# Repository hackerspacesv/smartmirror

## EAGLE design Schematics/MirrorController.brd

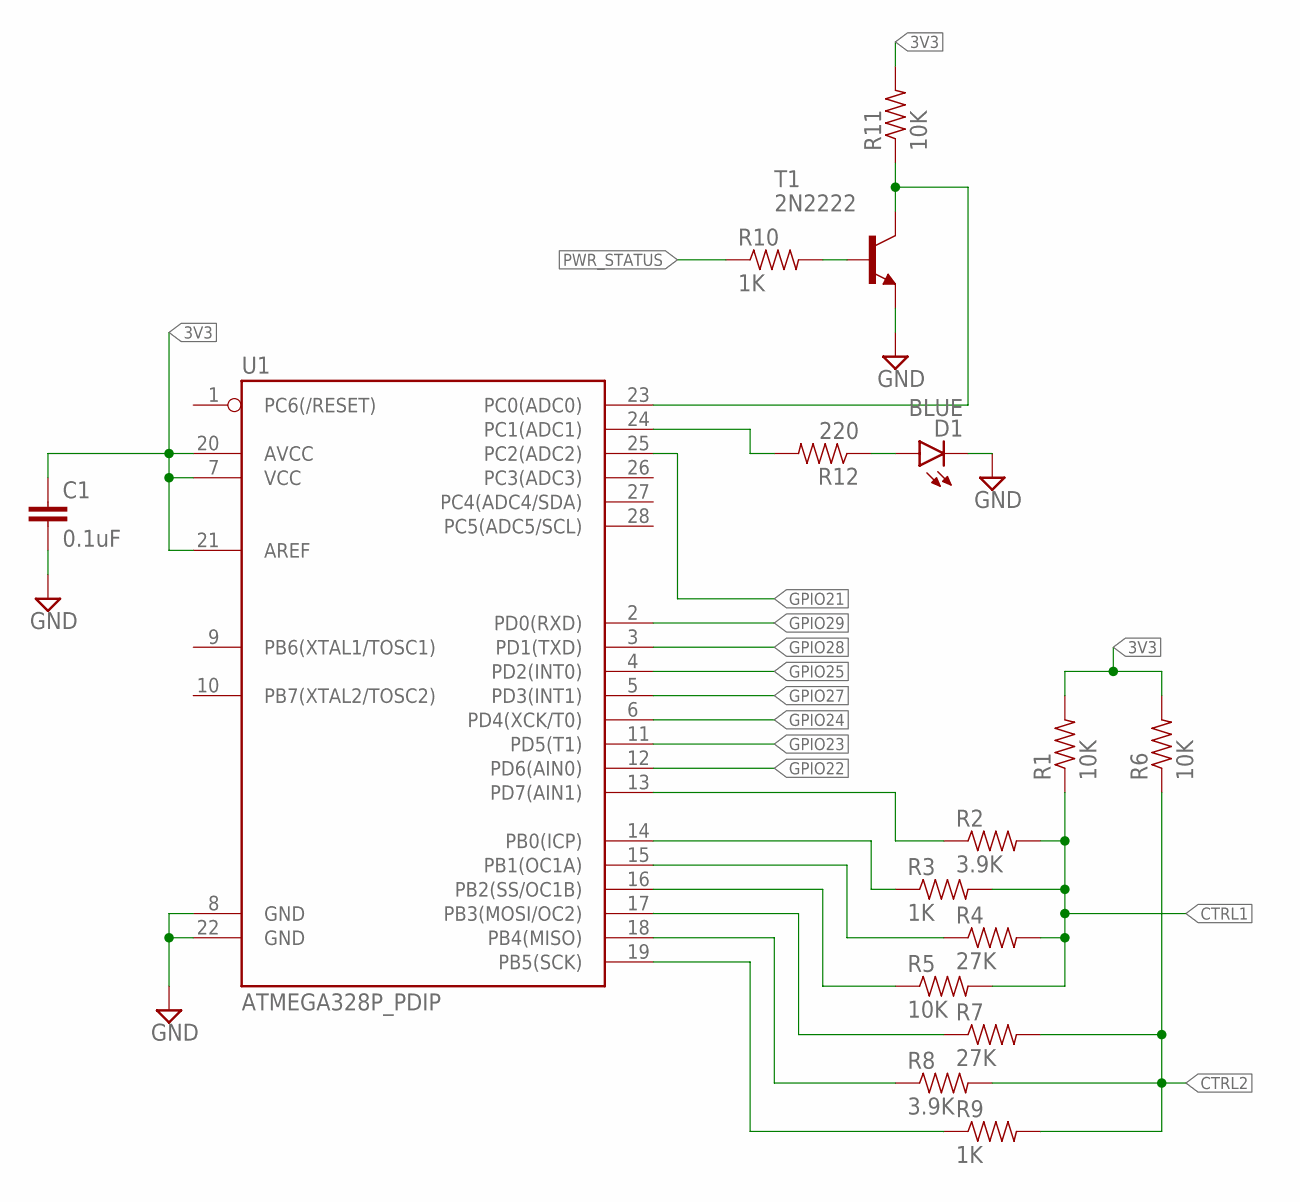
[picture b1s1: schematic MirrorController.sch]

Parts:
C1: 0.1uF; CAP-PTH-SMALL
D1: BLUE; LED5MM
R1, R5, R6, R11: 10K; AXIAL-0.4
R2, R8: 3.9K; AXIAL-0.4
R3, R9, R10: 1K; AXIAL-0.4
R4, R7: 27K; AXIAL-0.4
R12: 220; AXIAL-0.4
T1: 2N2222; TO92-EBC-OVAL
U1: ATMEGA328P_PDIP; DIL28-3

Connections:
3V3: C1.1, R1.P$2 (2), R6.P$2 (2), R11.P$2 (2), U1.7 (VCC), U1.20 (AVCC), U1.21 (AREF)
CTRL1: R1.P$1 (1), R2.P$2 (2), R3.P$2 (2), R4.P$2 (2), R5.P$2 (2)
CTRL2: R6.P$1 (1), R7.P$2 (2), R8.P$2 (2), R9.P$2 (2)
GND: C1.2, D1.K (C), T1.E, U1.8 (GND), U1.22 (GND)
GPIO21: U1.25 (PC2(ADC2))
GPIO22: U1.12 (PD6(AIN0))
GPIO23: U1.11 (PD5(T1))
GPIO24: U1.6 (PD4(XCK/T0))
GPIO25: U1.4 (PD2(INT0))
GPIO27: U1.5 (PD3(INT1))
GPIO28: U1.3 (PD1(TXD))
GPIO29: U1.2 (PD0(RXD))
unnamed: R2.P$1 (1), U1.13 (PD7(AIN1))
unnamed: R3.P$1 (1), U1.14 (PB0(ICP))
unnamed: R4.P$1 (1), U1.15 (PB1(OC1A))
unnamed: R5.P$1 (1), U1.16 (PB2(SS/OC1B))
unnamed: R7.P$1 (1), U1.17 (PB3(MOSI/OC2))
unnamed: R8.P$1 (1), U1.18 (PB4(MISO))
unnamed: R9.P$1 (1), U1.19 (PB5(SCK))
unnamed: R10.P$2 (2), T1.B
unnamed: R11.P$1 (1), T1.C, U1.23 (PC0(ADC0))
unnamed: D1.A, R12.P$1 (1)
unnamed: R12.P$2 (2), U1.24 (PC1(ADC1))
PWR_STATUS: R10.P$1 (1)

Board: 2 copper layers, 16 parts (0 on the bottom side), 15 nets, no tracks yet.

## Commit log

2016-07-07 added Schematic diagrams
2016-07-11 Added hardware to control TV and Sketch
2016-07-14 +I2C Support and temp files removed

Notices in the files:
parts and their libraries:
SparkFun-Resistors: Licensing: Creative Commons ShareAlike 4.0 International - https://creativecommons.org/licenses/by-sa/4.0
